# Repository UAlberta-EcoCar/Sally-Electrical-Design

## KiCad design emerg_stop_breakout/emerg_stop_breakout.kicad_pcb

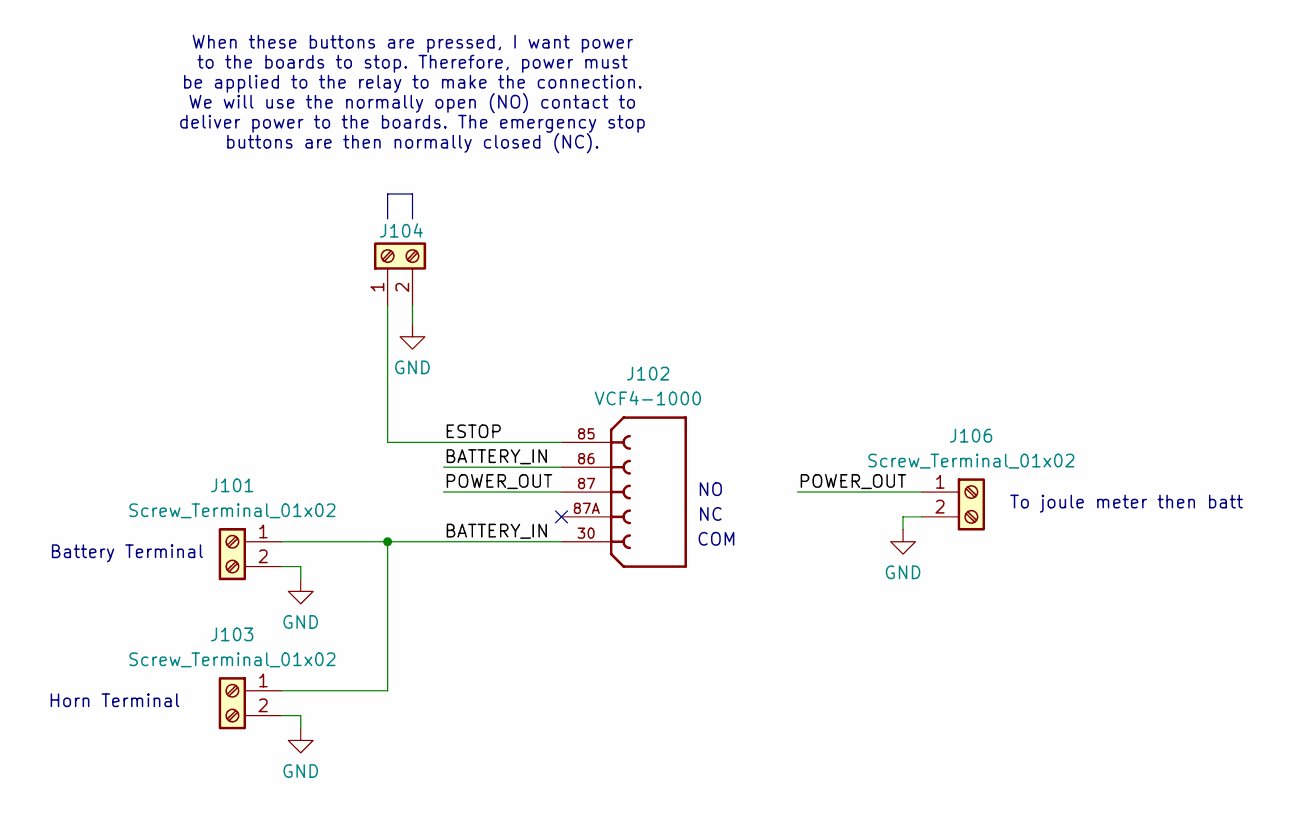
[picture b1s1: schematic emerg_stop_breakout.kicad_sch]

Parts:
J101, J103, J104, J106: Screw_Terminal_01x02; CONN2_1102030_OST
J102: VCF4-1000; TE_VCF4-1000; PARTREV B

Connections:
/BATTERY_IN: J101.1, J102.30, J102.86, J103.1
/ESTOP: J102.85, J104.1
/POWER_OUT: J102.87, J106.1
GND: J101.2, J103.2, J104.2, J106.2

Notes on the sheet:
Battery Terminal
COM
When these buttons are pressed, I want power to the boards to stop. Therefore, power must be applied to the relay to make the connection. We will use the normally open (NO) contact to deliver power to the boards. The emergency stop buttons are then normally closed (NC).
To joule meter then batt
Horn Terminal

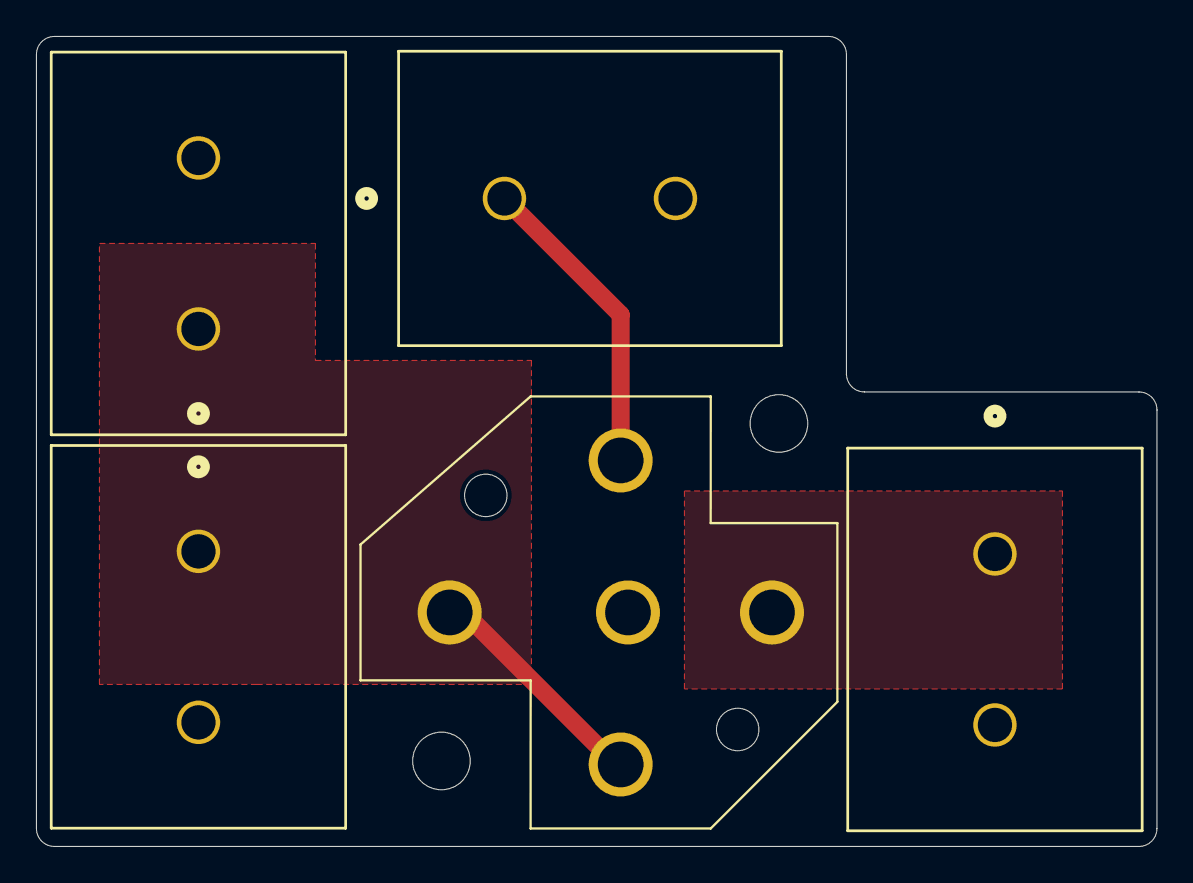
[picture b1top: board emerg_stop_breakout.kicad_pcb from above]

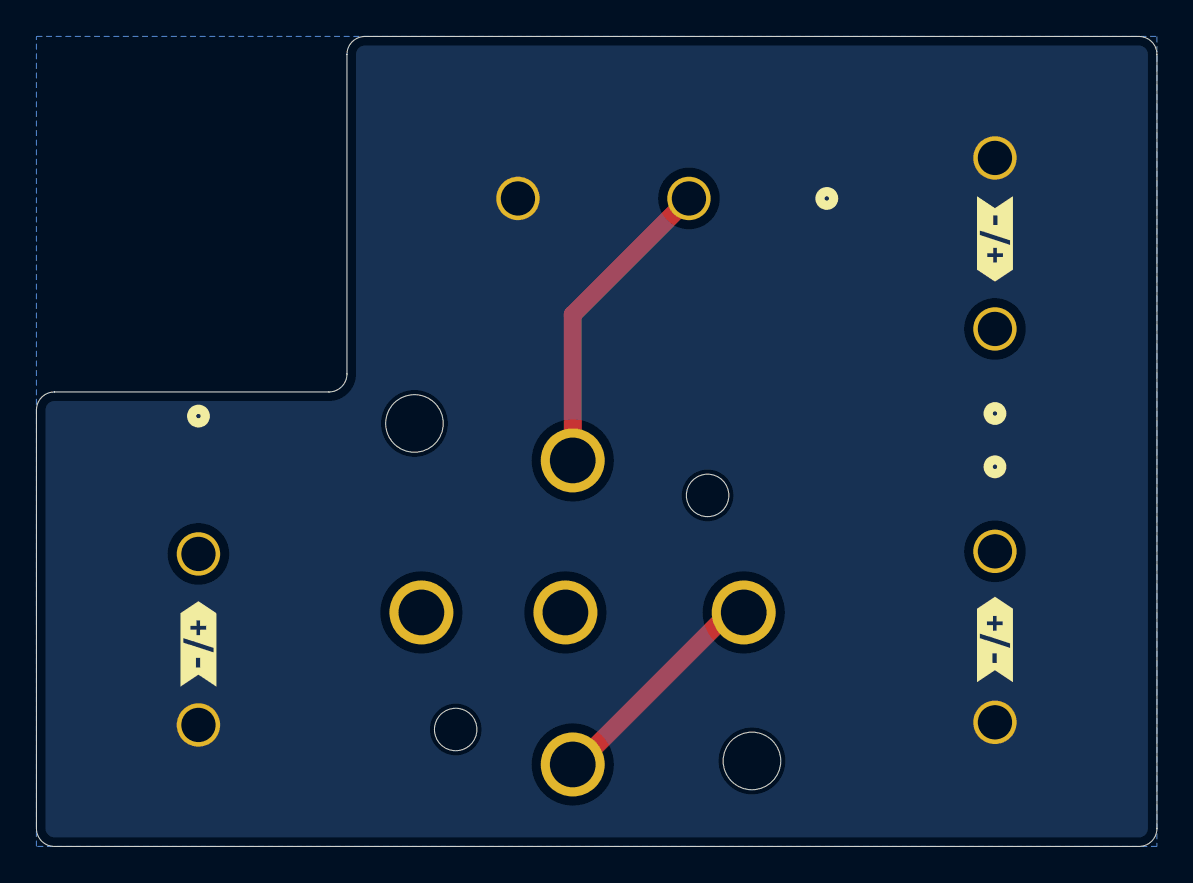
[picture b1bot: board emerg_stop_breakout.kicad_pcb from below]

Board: 2 copper layers, 62.2 x 45.0 mm, 8 parts (3 on the bottom side), 4 nets.

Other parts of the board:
kibuzzard-6786C6AF, kibuzzard-6786C6AF#2, kibuzzard-6786C6AF#3: G***; kibuzzard-6786C6AF

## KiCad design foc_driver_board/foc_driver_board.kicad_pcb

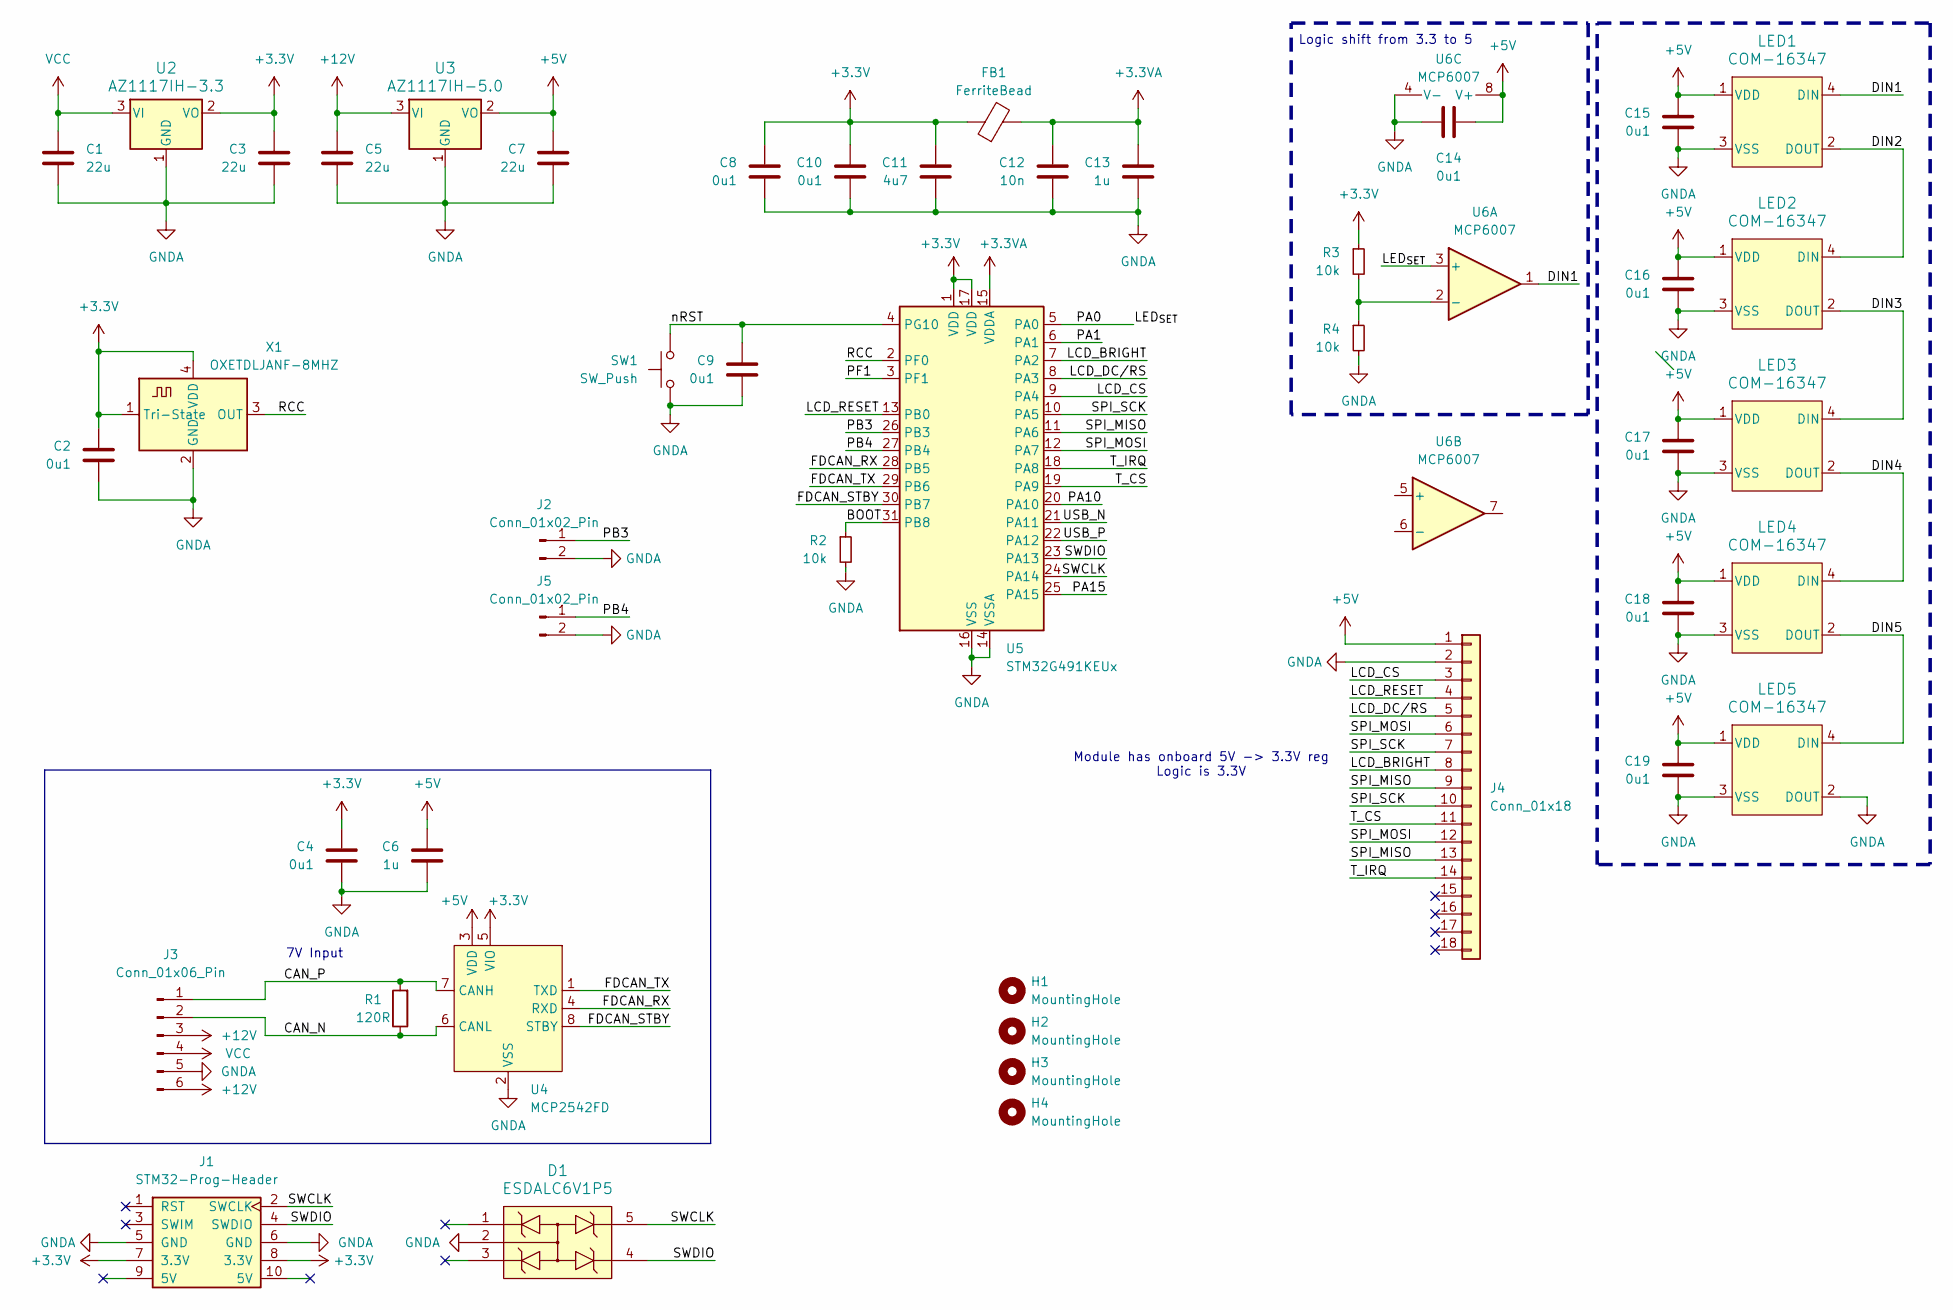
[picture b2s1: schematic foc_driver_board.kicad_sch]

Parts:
C1, C3, C5, C7: 22u; C_0603_1608Metric
C2, C4, C8, C9, C10, C14, C15, C16, C17, C18, C19: 0u1; C_0603_1608Metric
C6, C13: 1u; C_0603_1608Metric
C11: 4u7; C_0603_1608Metric
C12: 10n; C_0603_1608Metric
D1: ESDALC6V1P5
FB1: FerriteBead; L_0603_1608Metric
H1, H2, H3, H4: MountingHole; MountingHole_3.2mm_M3
J1: STM32-Prog-Header; IDC-STM32-Prog-Header_2x05_P2.54mm_Vertical
J2, J5: Conn_01x02_Pin; PinSocket_1x02_P2.54mm_Vertical
J3: Conn_01x06_Pin; STD_PWR_HEADER
J4: Conn_01x18; ILI9488
LED1, LED2, LED3, LED4, LED5: COM-16347; COM-16347_SPK
R1: 120R; R_0603_1608Metric
R2, R3, R4: 10k; R_0603_1608Metric
SW1: SW_Push; SW_PUSH_6mm
U2: AZ1117IH-3.3; SOT-223-3_TabPin2
U3: AZ1117IH-5.0; SOT-223-3_TabPin2
U4: MCP2542FD; SOIC-8_3.9x4.9mm_P1.27mm
U5: STM32G491KEUx; QFN-32-1EP_5x5mm_P0.5mm_EP3.45x3.45mm
U6: MCP6007; SOIC-8_3.9x4.9mm_P1.27mm
X1: OXETDLJANF-8MHZ; Crystal_SMD_3225-4Pin_3.2x2.5mm

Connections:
+3.3V: C2.1, C3.1, C4.1, C8.1, C10.1, C11.1, FB1.1, J1.7 (3.3V), J1.8 (3.3V), R3.1, U2.2 (VO), U4.5 (VIO), U5.1 (VDD), U5.17 (VDD), X1.1 (Tri-State), X1.4 (VDD)
+3.3VA: C12.1, C13.1, FB1.2, U5.15 (VDDA)
+5V: C6.1, C7.1, C14.1, C15.1, C16.1, C17.1, C18.1, C19.1, J4.1, LED1.1 (VDD), LED2.1 (VDD), LED3.1 (VDD), LED4.1 (VDD), LED5.1 (VDD), U3.2 (VO), U4.3 (VDD), U6.8 (V+)
+12V: C5.1, J3.3, J3.6, U3.3 (VI)
/BOOT: R2.1, U5.31 (PB8)
/CAN_N: J3.2, R1.1, U4.6 (CANL)
/CAN_P: J3.1, R1.2, U4.7 (CANH)
/DIN1: LED1.4 (DIN), U6.1
/DIN2: LED1.2 (DOUT), LED2.4 (DIN)
/DIN3: LED2.2 (DOUT), LED3.4 (DIN)
/DIN4: LED3.2 (DOUT), LED4.4 (DIN)
/DIN5: LED4.2 (DOUT), LED5.4 (DIN)
/FDCAN_RX: U4.4 (RXD), U5.28 (PB5)
/FDCAN_STBY: U4.8 (STBY), U5.30 (PB7)
/FDCAN_TX: U4.1 (TXD), U5.29 (PB6)
/LCD_BRIGHT: J4.8, U5.7 (PA2)
/LCD_CS: J4.3, U5.9 (PA4)
/LCD_DC/RS: J4.5, U5.8 (PA3)
/LCD_RESET: J4.4, U5.13 (PB0)
/LED_{SET}: U5.5 (PA0), U6.3 (+)
/PA1: U5.6 (PA1)
/PA10: U5.20 (PA10)
/PA15: U5.25 (PA15)
/PB3: J2.1, U5.26 (PB3)
/PB4: J5.1, U5.27 (PB4)
/PF1: U5.3 (PF1)
/RCC: U5.2 (PF0), X1.3 (OUT)
/SPI_MISO: J4.9, J4.13, U5.11 (PA6)
/SPI_MOSI: J4.6, J4.12, U5.12 (PA7)
/SPI_SCK: J4.7, J4.10, U5.10 (PA5)
/SWCLK: D1.5, J1.2 (SWCLK), U5.24 (PA14)
/SWDIO: D1.4, J1.4 (SWDIO), U5.23 (PA13)
/T_CS: J4.11, U5.19 (PA9)
/T_IRQ: J4.14, U5.18 (PA8)
/USB_N: U5.21 (PA11)
/USB_P: U5.22 (PA12)
/nRST: C9.1, SW1.2, U5.4 (PG10)
GNDA: C1.2, C2.2, C3.2, C4.2, C5.2, C6.2, C7.2, C8.2, C9.2, C10.2, C11.2, C12.2, C13.2, C14.2, C15.2, C16.2, C17.2, C18.2, C19.2, D1.2, J1.5 (GND), J1.6 (GND), J2.2, J3.5, J4.2, J5.2, LED1.3 (VSS), LED2.3 (VSS), LED3.3 (VSS), LED4.3 (VSS), LED5.2 (DOUT), LED5.3 (VSS), R2.2, R4.2, SW1.1, U2.1 (GND), U3.1 (GND), U4.2 (VSS), U5.14 (VSSA), U5.16 (VSS), U5.32 (VSS), U5.33 (VSS), U6.4 (V-), X1.2 (GND)
unnamed: R3.2, R4.1, U6.2 (-)
VCC: C1.1, J3.4, U2.3 (VI)

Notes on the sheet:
Logic shift from 3.3 to 5
7V Input
Module has onboard 5V -> 3.3V reg Logic is 3.3V

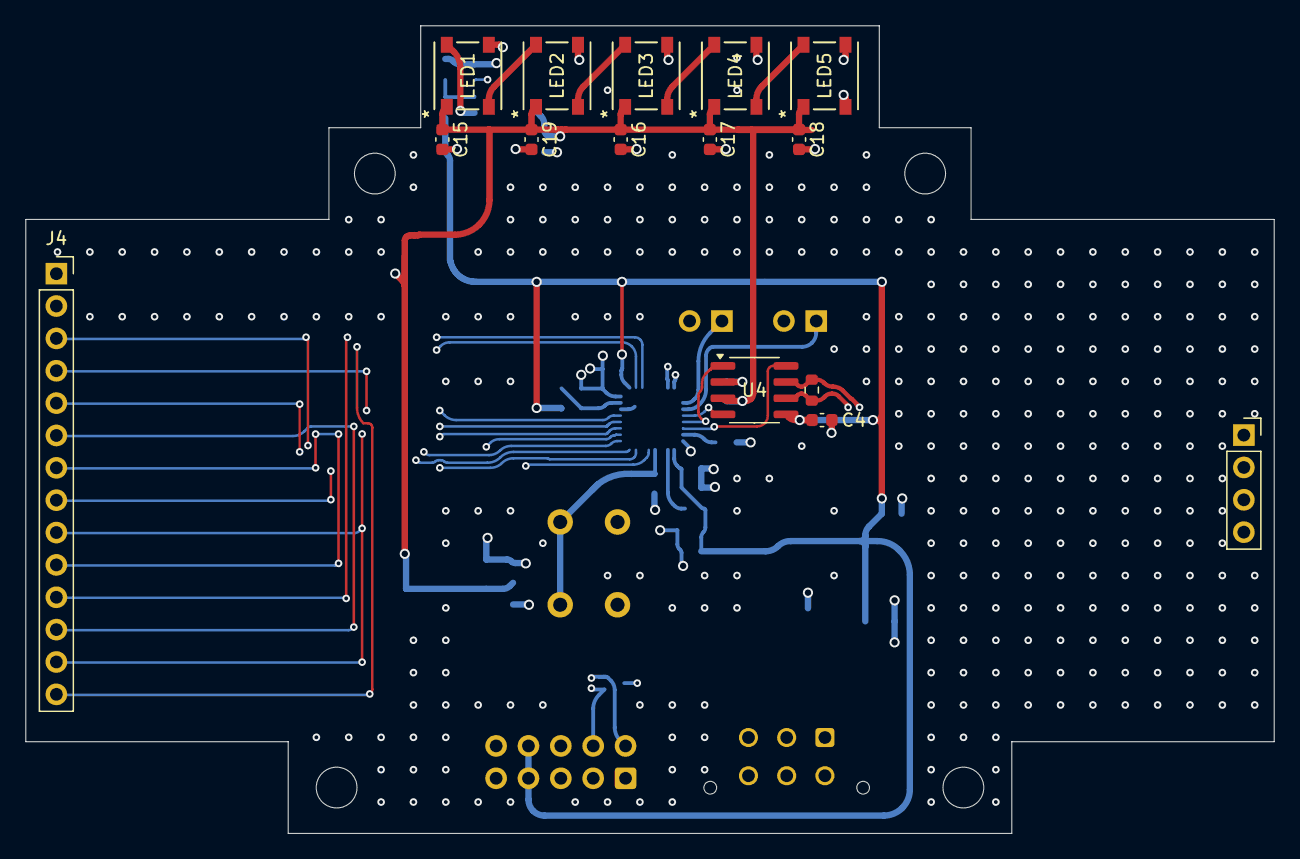
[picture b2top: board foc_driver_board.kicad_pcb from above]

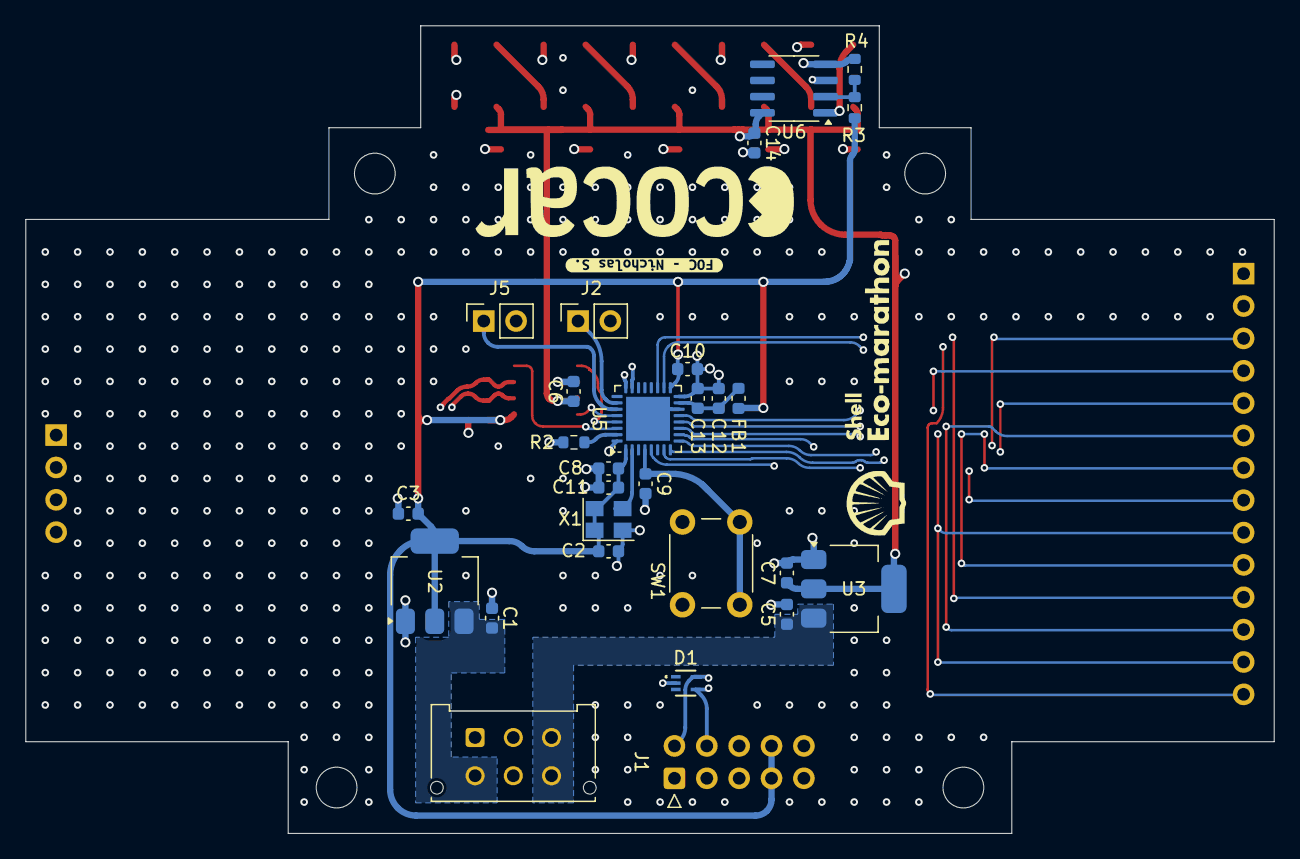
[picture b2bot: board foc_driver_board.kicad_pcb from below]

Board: 4 copper layers, 98.0 x 63.4 mm, 47 parts (29 on the bottom side), 34 nets.

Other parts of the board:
kibuzzard-678986CF: G***; kibuzzard-678986CF

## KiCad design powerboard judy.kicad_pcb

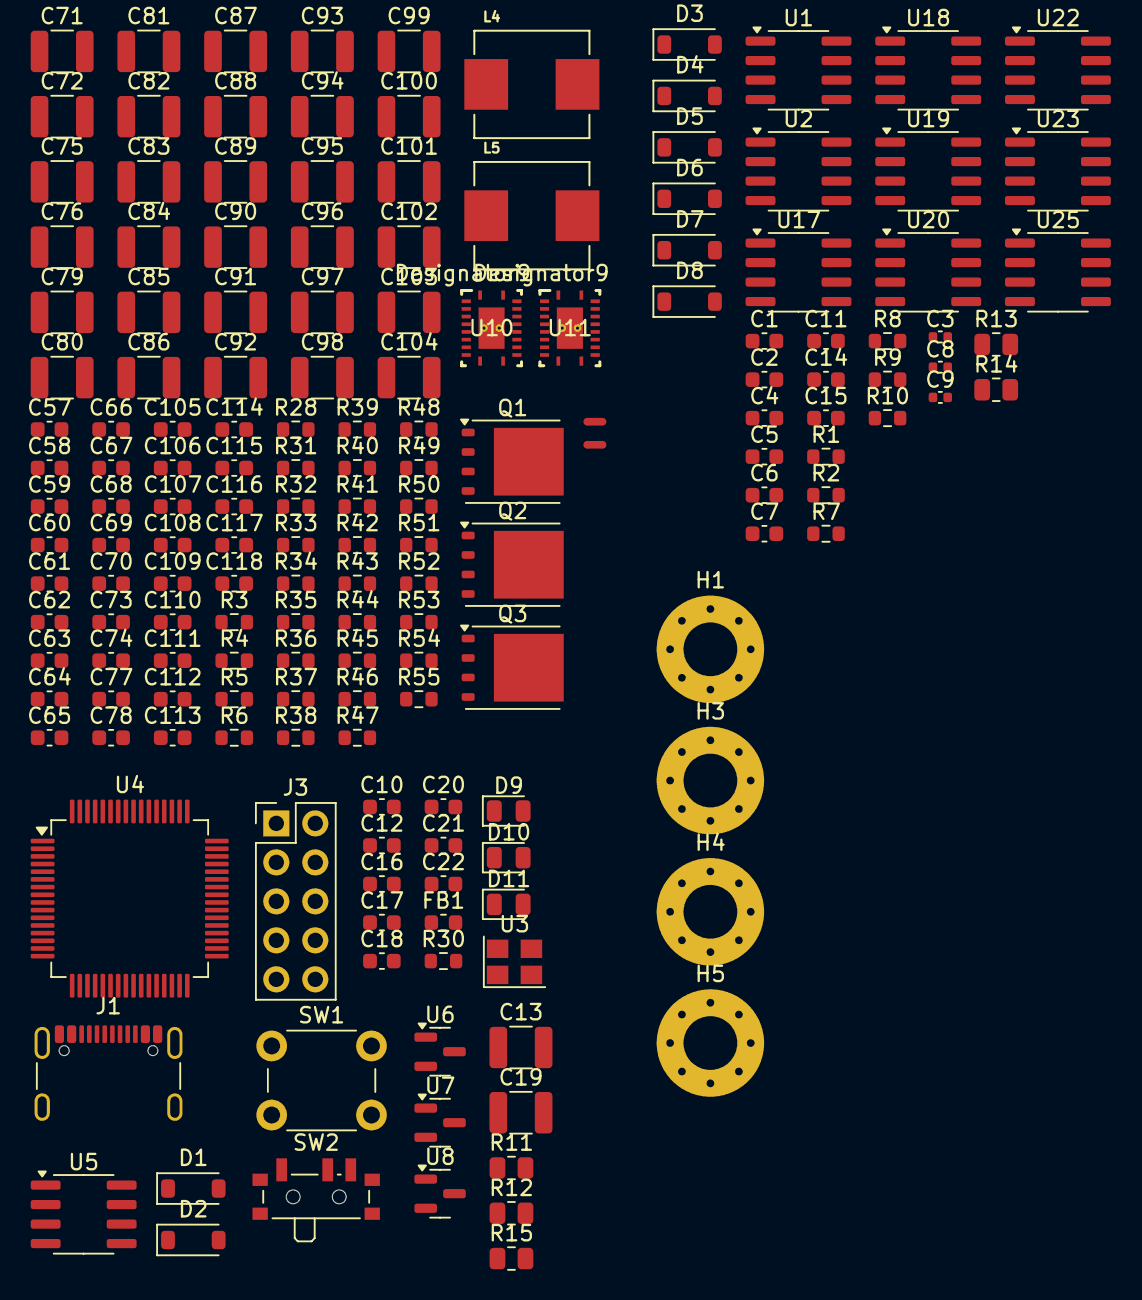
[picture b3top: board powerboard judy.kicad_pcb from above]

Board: 2 copper layers, 170 parts (0 on the bottom side), 81 nets, no tracks yet.

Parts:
C1, C4, C5, C10, C11, C12, C14, C15, C16, C17, C18, C21, C59, C60, C63, C64, C105, C106, C109, C110, C111, C112, C113, C114, C115, C116, C117, C118: 100n; C_0603_1608Metric
C2: 1u5; C_0603_1608Metric
C3, C8, C9: 1n; C_0402_1005Metric
C6, C20, C22: 1u; C_0603_1608Metric
C7: 6.8u; C_0603_1608Metric
C13, C19, C71, C72, C75, C76, C79, C80, C81, C82, C83, C84, C85, C86, C87, C88, C89, C90, C91, C92, C93, C94, C95, C96, C97, C98, C99, C100, C101, C102, C103, C104: 10u; C_1210_3225Metric
C57, C58, C73, C74: C; C_0603_1608Metric
C61, C62: 47n; C_0603_1608Metric
C65, C66: 15pF; C_0603_1608Metric
C67, C68: 5600pF; C_0603_1608Metric
C69, C70: 150pF; C_0603_1608Metric
C77, C78: 1800pF; C_0603_1608Metric
C107, C108: 220u; C_0603_1608Metric
D1, D3, D4, D5, D6, D7, D8: MMSZ5226B-7-F; D_SOD-123
D2: MMSZ5231B-7-F; D_SOD-123
D9: AMBER; LED_0805_2012Metric
D10: RED; LED_0805_2012Metric
D11: GREEN; LED_0805_2012Metric
FB1: 300R; L_0603_1608Metric
H1, H3, H4, H5: MountingHole; MountingHole_3.5mm_Pad_Via
J1: USB_C_Receptacle_USB2.0_16P; USB_C_Receptacle_GCT_USB4105-xx-A_16P_TopMnt_Horizontal
J3: GPIO; PinHeader_2x05_P2.54mm_Vertical
L4, L5: 22u; IND_SPM7054VC-220M-D
NT3, NT4: NetTie_2; NetTie-2_SMD_Pad0.5mm
Q1, Q2, Q3: CSD18563Q5A; TDSON-8-1
R1: 13k6; R_0603_1608Metric
R2, R9: 4k7; R_0603_1608Metric
R3, R4, R5, R6: 0; R_0603_1608Metric
R7: 28k7; R_0603_1608Metric
R8, R46, R47: 10k; R_0603_1608Metric
R10: 1k02; R_0603_1608Metric
R11, R12, R15: 220R; R_0805_2012Metric
R13, R14: 47k; R_0805_2012Metric
R28, R31: 18.2k; R_0603_1608Metric
R30, R48, R49: R; R_0603_1608Metric
R32, R33: 301k; R_0603_1608Metric
R34, R35: 46.4k; R_0603_1608Metric
R36, R37, R38, R39, R50, R51: 20.0k; R_0603_1608Metric
R40, R41: 2.2; R_0603_1608Metric
R42, R43: 422; R_0603_1608Metric
R44, R45: 3.83k; R_0603_1608Metric
R52, R53: 1.00k; R_0603_1608Metric
R54, R55: 49.9; R_0603_1608Metric
SW1: RESET; SW_PUSH_6mm_H5mm
SW2: SW_SPDT; SW_SPDT_PCM12
U1, U17, U18: ACS723xLCTR-10AU; SOIC-8_3.9x4.9mm_P1.27mm
U2, U19, U20, U22, U23, U25: MCP6007; SOIC-8_3.9x4.9mm_P1.27mm
U3: 8MHz; Crystal_SMD_3225-4Pin_3.2x2.5mm
U4: STM32G491RETx; LQFP-64_10x10mm_P0.5mm
U5: MCP2542FD-E/SN; SOIC-8_3.9x4.9mm_P1.27mm
U6, U7, U8: MCP9700AT-ETT; SOT-23
U10, U11: LM5145; RGY0020B

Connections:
+3.3VA: C19.1, C20.1, FB1.1, U4.29 (VDDA)
+3V3: C10.2, C13.1, C16.1, C17.1, C21.2, C22.1, D1.1 (K), FB1.2, J3.7, J3.8, SW2.3 (C), U3.1 (~ST), U3.4 (VCC), U4.1 (VBAT), U4.16 (VDD), U4.32 (VDD), U4.48 (VDD), U4.64 (VDD), U5.5 (VIO), U6.1 (V_{DD}), U7.1 (V_{DD}), U8.1 (V_{DD})
+5V: C1.1, C4.1, C5.2, C11.1, C14.1, C15.1, C18.2, D2.1 (K), J3.9, J3.10, R13.1, U1.8 (VCC), U5.3 (VDD), U17.8 (VCC), U18.8 (VCC), U22.8 (V+), U23.8 (V+), U25.8 (V+)
+18.5V: C71.1, C72.1, C75.1, C76.1, C81.1, C82.1, C85.1, C86.1, C89.1, C90.1, C93.1, C94.1, C97.1, C98.1, C101.1, C102.1, C105.1, C106.1, C109.1, C110.1, C113.1, C114.1, C115.1, C116.1, C117.1, C118.1, Q1.1 (S), Q1.2 (S), Q1.3 (S), R32.1, R33.1, R40.1, R41.1
/Microcontroller/12V_Current_Out: U4.19 (PA5), U4.21 (PA7)
/Microcontroller/BOOT0: SW2.2 (B), U4.61 (PB8)
/Microcontroller/BUCK_TEMP_SENSE: U4.12 (PA0), U6.2 (V_{OUT})
/Microcontroller/CNTLR_TEMP_SENSE: U4.14 (PA2), U8.2 (V_{OUT})
/Microcontroller/DEBUG_SWCLK: J3.2, U4.50 (PA14)
/Microcontroller/DEBUG_SWDIO: J3.4, U4.49 (PA13)
/Microcontroller/GPLED1: R11.2, U4.2 (PC13)
/Microcontroller/GPLED2: R12.2, U4.3 (PC14)
/Microcontroller/GPLED3: R15.2, U4.4 (PC15)
/Microcontroller/NRST: C12.2, SW1.2, U4.7 (PG10)
/Microcontroller/O/P_TEMP_SENSE: U4.13 (PA1), U7.2 (V_{OUT})
/Microcontroller/USB_DM: J1.A7 (D-), J1.B7 (D-), U4.45 (PA11)
/Microcontroller/USB_DP: J1.A6 (D+), J1.B6 (D+), U4.46 (PA12)
/Microcontroller/XCLK: U3.3 (OUT), U4.5 (PF0)
/Microcontroller/power/12V_Current_Out: U2.1, U2.2 (-), U20.1, U20.2 (-)
/Microcontroller/power/12V_PCBs: U1.3 (IP-), U1.4 (IP-), U17.3 (IP-), U17.4 (IP-)
/Microcontroller/power/12V_Unsensed: R1.1, R7.1, U1.1 (IP+), U1.2 (IP+), U17.1 (IP+), U17.2 (IP+)
/Microcontroller/power/ADC_BUCK_7V_Out: U2.6 (-), U2.7
/Microcontroller/power/ADC_BUCK_12V_OUT: U20.6 (-), U20.7
/Microcontroller/power/ADC_Battery_Voltage: U19.6 (-), U19.7
/Microcontroller/power/Battery_Crrnt: U19.1, U19.2 (-)
/Microcontroller/power/Battery_Terminal: U18.3 (IP-), U18.4 (IP-)
/Microcontroller/power/Battery_Terminal_Unsensed: R8.1, U18.1 (IP+), U18.2 (IP+)
/Microcontroller/power/u11_unused: R13.2, R14.1
GND: C1.2, C2.2, C3.2, C4.2, C5.1, C6.2, C7.2, C8.2, C9.2, C11.2, C12.1, C13.2, C14.2, C15.2, C16.2, C17.2, C18.1, C19.2, C20.2, C21.1, C22.2, C57.1, C58.1, C61.1, C62.1, D1.2 (A), D2.2 (A), D3.2 (A), D4.2 (A), D5.2 (A), D6.2 (A), D7.2 (A), D8.2 (A), D9.1 (K), D10.1 (K), D11.1 (K), J1.A1 (GND), J1.A12 (GND), J1.B1 (GND), J1.B12 (GND), J1.S1 (SHIELD), J3.5, J3.6, NT3.1, NT4.1, R2.2, R9.2, R10.2, R14.2, R28.1, R31.1, R34.2, R35.2, R44.1, R45.1, SW1.1, SW2.1 (A), U1.5 (GND), U1.6 (BW_SEL), U4.15 (VSS), U4.27 (VSSA), U4.31 (VSS), U4.47 (VSS), U4.63 (VSS), U5.2 (VSS), U6.3 (GND), U7.3 (GND), U8.3 (GND), U10.6 (AGND), U11.6 (AGND), U17.5 (GND), U17.6 (BW_SEL), U18.5 (GND), U18.6 (BW_SEL), U22.4 (V-), U23.4 (V-), U25.4 (V-)
GNDPWR: C59.1, C60.1, C65.1, C66.1, C71.2, C72.2, C75.2, C76.2, C79.2, C80.2, C81.2, C82.2, C83.2, C84.2, C85.2, C86.2, C87.2, C88.2, C89.2, C90.2, C91.2, C92.2, C93.2, C94.2, C95.2, C96.2, C97.2, C98.2, C99.2, C100.2, C101.2, C102.2, C103.2, C104.2, C105.2, C106.2, C107.2, C108.2, C109.2, C110.2, C111.2, C112.2, C113.2, C114.2, C115.2, C116.2, C117.2, C118.2, NT3.2, NT4.2, Q2.1 (S), Q2.2 (S), Q2.3 (S), Q3.1 (S), Q3.2 (S), Q3.3 (S), R48.1, R49.1, U10.9 (NC), U10.12 (PGND), U10.15 (EP), U10.16 (NC), U10.21 (EP), U11.9 (NC), U11.12 (PGND), U11.15 (EP), U11.16 (NC), U11.21 (EP)
unnamed: C67.2, R46.1
unnamed: C68.2, R47.1
unnamed: C73.2, R48.2
unnamed: C74.2, R49.2
unnamed: C77.2, R52.1
unnamed: C78.2, R53.1
unnamed: C80.1, C84.1, C88.1, C92.1, C96.1, C100.1, C104.1, C108.1, C112.1, L5.2, R55.2
unnamed: C79.1, C83.1, C87.1, C91.1, C95.1, C99.1, C103.1, C107.1, C111.1, L4.2, R54.2
unnamed: C2.1, D3.1 (K), R1.2, R2.1, U2.5 (+)
unnamed: C3.1, D4.1 (K), U1.7 (VIOUT), U2.3 (+)
unnamed: C6.1, D5.1 (K), R7.2, R9.1, U20.5 (+)
unnamed: C7.1, D6.1 (K), R8.2, R10.1, U19.5 (+)
unnamed: C8.1, D7.1 (K), U17.7 (VIOUT), U20.3 (+)
unnamed: C9.1, D8.1 (K), U18.7 (VIOUT), U19.3 (+)
unnamed: D9.2 (A), R11.1
unnamed: D10.2 (A), R12.1
unnamed: D11.2 (A), R15.1
unnamed: C63.1, C63.2, C73.1, L4.1, Q1.5 (D), R42.2, U10.17 (BST), U10.19 (SW)
unnamed: Q1.4 (G), R4.2
unnamed: C64.1, C64.2, C74.1, L5.1, Q2.5 (D), Q3.5 (D), R43.2, U11.17 (BST), U11.19 (SW)
unnamed: Q2.4 (G), Q3.4 (G), R6.2
unnamed: R50.2, R52.2, R54.1
unnamed: R51.2, R53.2, R55.1
unnamed: C10.1, U3.2 (GND)
unnamed: R30.1, U5.7 (CANH)
unnamed: R30.2, U5.6 (CANL)
unnamed: C67.1, C69.1, U10.4 (COMP)
unnamed: R28.2, R32.2, U10.1 (EN_UVLO)
unnamed: C69.2, C77.1, R44.2, R46.2, R50.1, U10.5 (FB)
unnamed: R4.1, U10.18 (HO)
unnamed: C65.2, R42.1, U10.11 (ILIM)
unnamed: R3.1, U10.13 (LO)
unnamed: R37.2, U10.10 (PGOOD)
unnamed: R34.1, U10.2 (RT)
unnamed: C61.2, U10.3 (SS_TRK)
unnamed: R36.1, U10.8 (SYNCIN)
unnamed: C57.2, R36.2, R37.1, U10.14 (VCC)
unnamed: C59.2, R40.2, U10.20 (VIN)
unnamed: C68.1, C70.1, U11.4 (COMP)
unnamed: R31.2, R33.2, U11.1 (EN_UVLO)
unnamed: C70.2, C78.1, R45.2, R47.2, R51.1, U11.5 (FB)
unnamed: R5.1, U11.18 (HO)
unnamed: C66.2, R43.1, U11.11 (ILIM)
unnamed: R6.1, U11.13 (LO)
unnamed: R39.2, U11.10 (PGOOD)
unnamed: R35.1, U11.2 (RT)
unnamed: C62.2, U11.3 (SS_TRK)
unnamed: R38.1, U11.8 (SYNCIN)
unnamed: C58.2, R38.2, R39.1, U11.14 (VCC)
unnamed: C60.2, R41.2, U11.20 (VIN)
VBUS: J1.A4 (VBUS), J1.A9 (VBUS), J1.B4 (VBUS), J1.B9 (VBUS)
